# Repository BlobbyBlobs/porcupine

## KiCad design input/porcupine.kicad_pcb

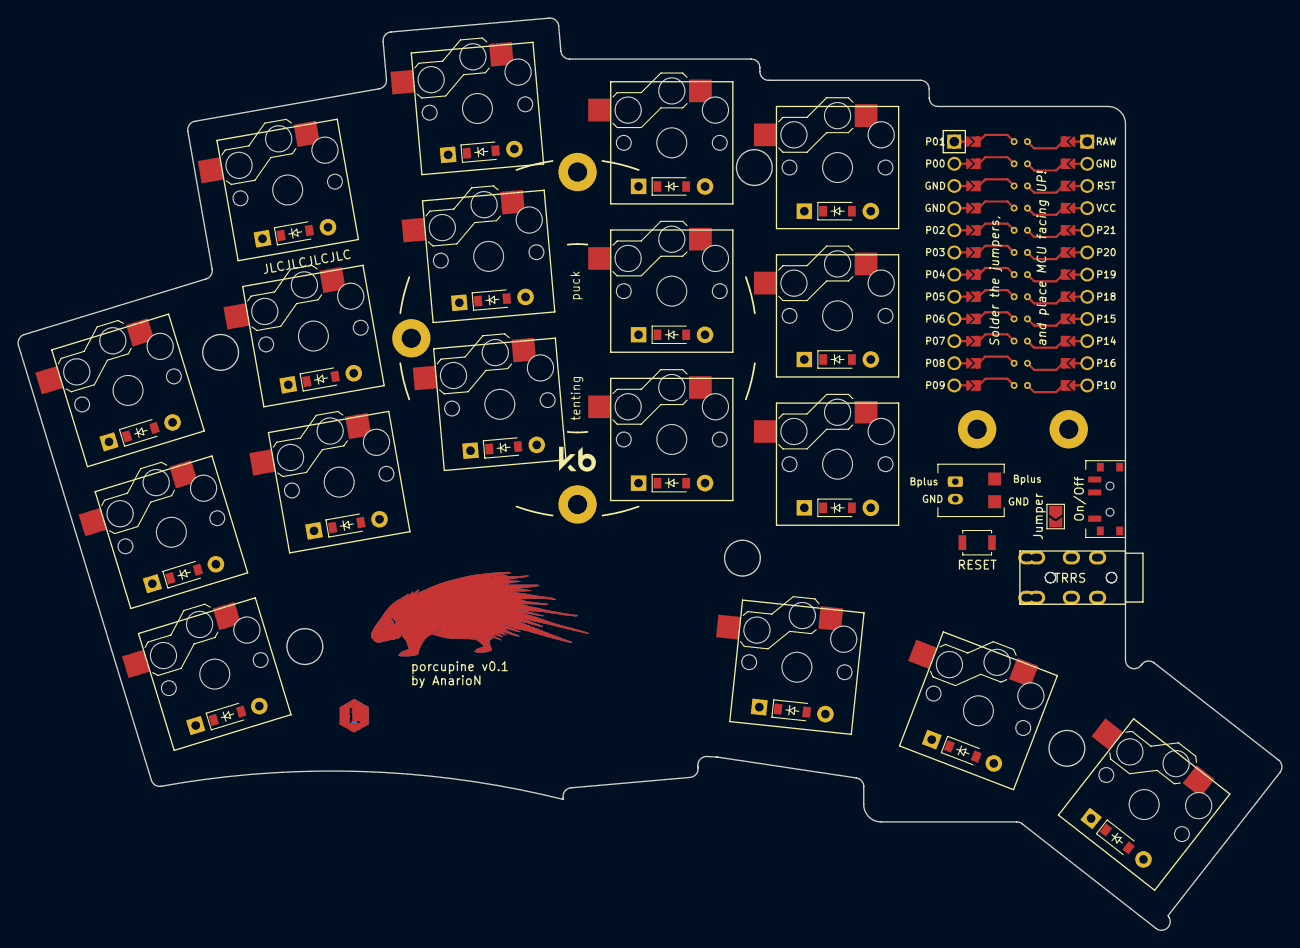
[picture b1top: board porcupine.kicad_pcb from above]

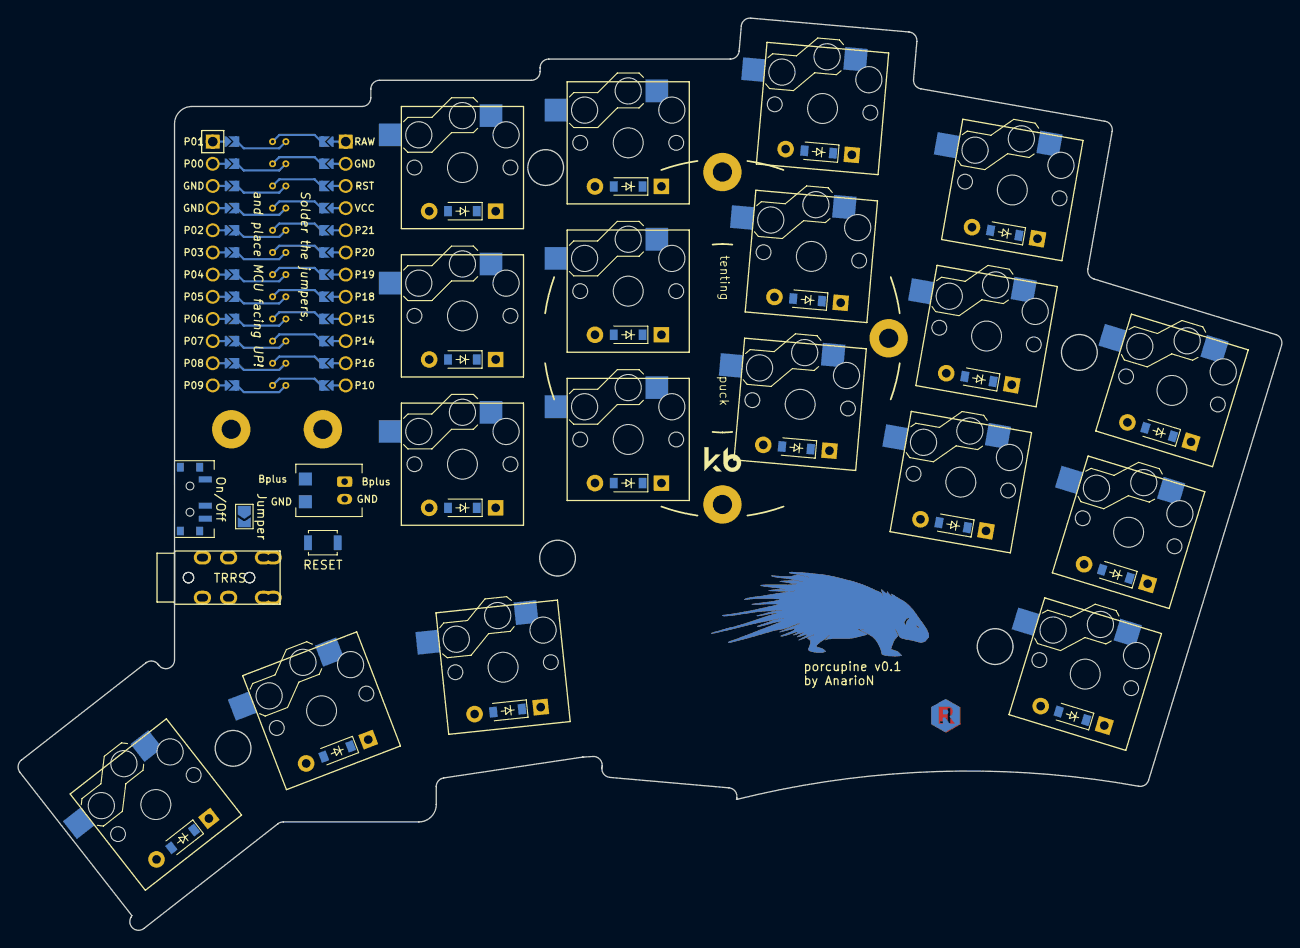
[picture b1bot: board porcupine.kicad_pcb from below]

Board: 2 copper layers, 144.8 x 104.6 mm, 54 parts (5 on the bottom side), 32 nets, no tracks yet.

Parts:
D1, D2, D3, D4, D5, D6, D7, D8, D9, D10, D11, D12, D13, D14, D15, D16, D17, D18: D_SOD-123; SOD-123
J1, J2: Jumper; SolderJumper-2_P1.3mm_Open_TrianglePad1.0x1.5mm
LOGO_B: Porcupine Logo
LOGO_F: Porcupine Logo
MCU1: ProMicro
PAD1, PAD2: SMDPad
S1, S2, S3, S4, S5, S6, S7, S8, S9, S10, S11, S12, S13, S14, S15, S16, S17, S18: PG1350
Side_B: Side Indicator
Side_F: Side Indicator
TRRS_B: AudioJack4; TRRS-PJ-320A-dual
TRRS_F: AudioJack4; TRRS-PJ-320A-dual
_2: bat2p0
_3: SW_SPDT_PCM12
_4_B, _4_F: SW_Push; SW_SPST_B3U-1000P
_7: Tenting Puck
_71, _72: hole; Through Hole

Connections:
Bplus: J1.1, J2.1, PAD1.1, _2.1, _3.2
GND: MCU1.2, MCU1.21, MCU1.22, PAD2.1, TRRS_B.R1, _2.2, _4_B.2
P0: MCU1.23, TRRS_B.R2
P4: D3.1, D3.2, D6.1, D6.2, D9.1, D9.2, D12.1, D12.2, D15.1, D15.2, MCU1.18
P5: D2.1, D2.2, D5.1, D5.2, D8.1, D8.2, D11.1, D11.2, D14.1, D14.2, MCU1.17
P6: D1.1, D1.2, D4.1, D4.2, D7.1, D7.2, D10.1, D10.2, D13.1, D13.2, MCU1.16
P14: MCU1.10, S13.2, S14.2, S15.2, S18.2
P15: MCU1.9, S10.2, S11.2, S12.2, S17.2
P18: MCU1.8, S7.2, S8.2, S9.2, S16.2
P19: MCU1.7, S4.2, S5.2, S6.2
P20: MCU1.6, S1.2, S2.2, S3.2
RAW: J1.2, J2.2, MCU1.1, _3.1
RST: MCU1.3, _4_B.1
VCC: MCU1.4, TRRS_B.S, TRRS_B.T
far_thumb: D18.1, D18.2, S18.1
home_thumb: D17.1, D17.2, S17.1
index_bottom: D10.1, D10.2, S10.1
index_home: D11.1, D11.2, S11.1
index_top: D12.1, D12.2, S12.1
inner_bottom: D13.1, D13.2, S13.1
inner_home: D14.1, D14.2, S14.1
inner_top: D15.1, D15.2, S15.1
middle_bottom: D7.1, D7.2, S7.1
middle_home: D8.1, D8.2, S8.1
middle_top: D9.1, D9.2, S9.1
near_thumb: D16.1, D16.2, S16.1
pinky_bottom: D1.1, D1.2, S1.1
pinky_home: D2.1, D2.2, S2.1
pinky_top: D3.1, D3.2, S3.1
ring_bottom: D4.1, D4.2, S4.1
ring_home: D5.1, D5.2, S5.1
ring_top: D6.1, D6.2, S6.1

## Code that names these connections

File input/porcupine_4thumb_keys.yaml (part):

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          ref: matrix_pinky_top
          shift: [-5,8]
        params:
          net: pinky_top
      via_P20_2:
        what: simple_via
        adjust:
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          ref: matrix_pinky_home
          shift: [0,8.5]
        params:
          net: pinky_home
      via_P20_3:
        what: simple_via
        adjust:
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          ref: matrix_pinky_bottom
          shift: [0,8.5]
        params:
          net: pinky_bottom
      via_P19_1:
        what: simple_via
        adjust:
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
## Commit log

2024-04-26 Beschreibung deiner Änderungen
2024-05-01 Beschreibung deiner ÄnderungenOAO2
